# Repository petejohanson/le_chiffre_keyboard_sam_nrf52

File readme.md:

# DO NOT USE THIS YET

This is a fork of the awesome [Le Chiffre STM32 by Sporkus](https://github.com/sporkus/le_chiffre_keyboard_stm32/) refactored to
SAM L/D21 and a secondary nRF52805 BLE module that is COMPLETELY UNTESTED.

Don't print it, don't try it and ask why it doesn't work.

When it's ready and tested, this will be updated. Until then, just don't.

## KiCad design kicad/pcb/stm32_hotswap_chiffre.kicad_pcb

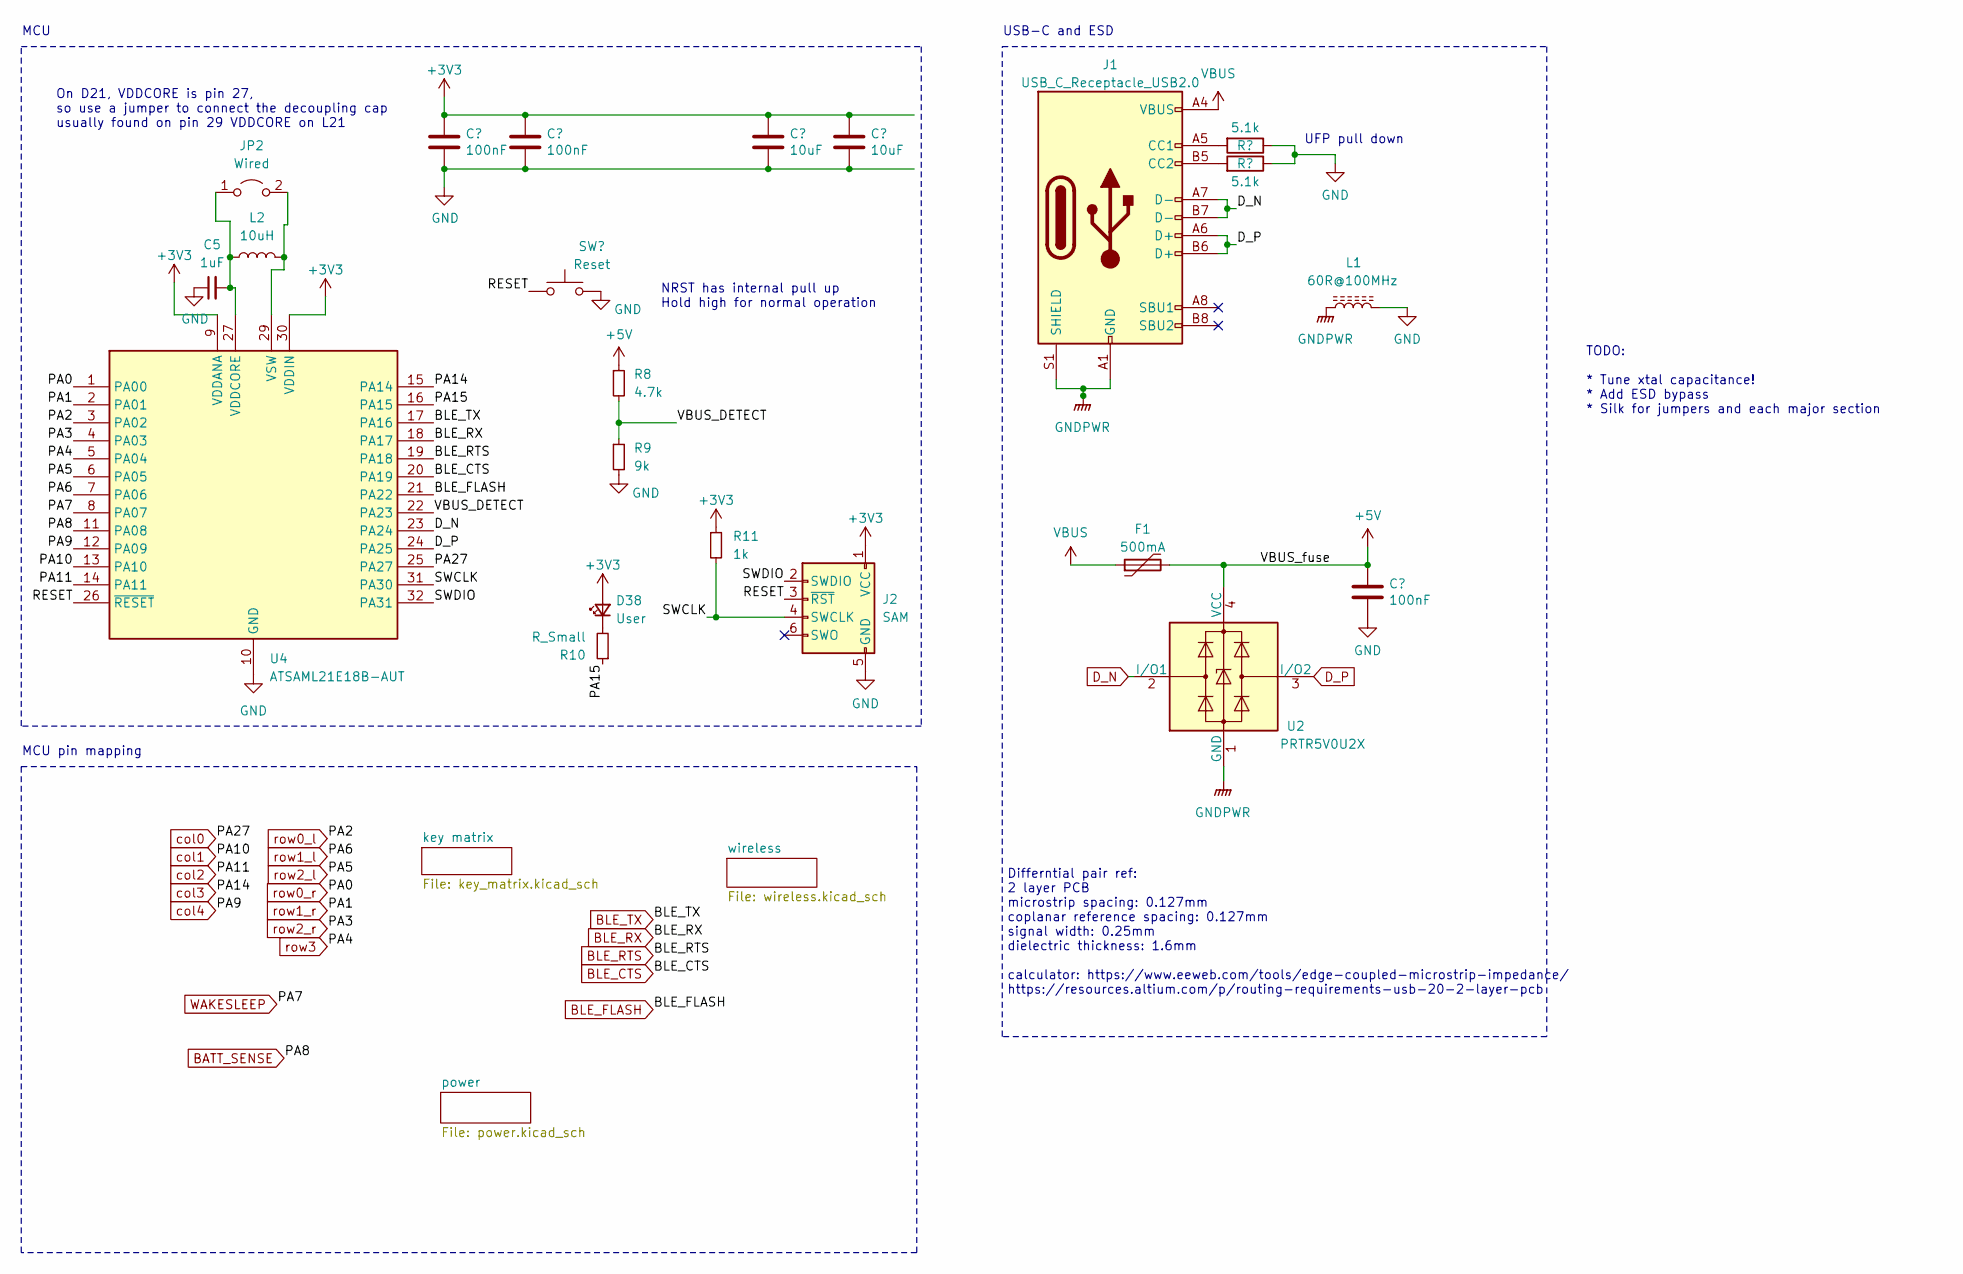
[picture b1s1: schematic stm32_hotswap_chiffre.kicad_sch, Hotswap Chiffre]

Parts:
C1, C2, C8: 100nF; C_0805_2012Metric; LCSC C38141
C3, C4: 10uF; C_0805_2012Metric; LCSC C17024
C5: 1uF; C_0805_2012Metric; LCSC C24123
D38: User; LED_0805_2012Metric; LCSC C84259
F1: 500mA; Fuse_1206_3216Metric; MPN BSMD1206-025-16V; LCSC C883119
J1: USB_C_Receptacle_USB2.0; USB_C_Receptacle_HRO_TYPE-C-31-M-12; MPN TYPE-C-31-M-12; JlcRotOffset 180
J2: SAM; CON_TC2030_outlined
JP2: Wired; SolderJumper-2_P1.3mm_Open_TrianglePad1.0x1.5mm
L1: 60R@100MHz; L_1206_3216Metric; MPN MLB3216-600P4A(f); LCSC C3033915
L2: 10uH; L_0805_2012Metric; LCSC C139245
R1, R2: 5.1k; R_0805_2012Metric; LCSC C118848
R8: 4.7k; R_0805_2012Metric; LCSC C228716
R9: 9k; R_0805_2012Metric; LCSC C2828721
R10: R_Small; R_0805_2012Metric; LCSC C2907256
R11: 1k; R_0805_2012Metric; LCSC C95781
SW37: Reset; SW_SPST_SKQG_WithoutStem; MPN SKQGABE010; LCSC C115351
U2: PRTR5V0U2X; SOT-143; MPN PRTR5V0U2X; LCSC C2827688
U4: ATSAML21E18B-AUT; TQFP-32_7x7mm_P0.8mm; MPN ATSAML21E18B-AUT; LCSC C2053723

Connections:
+5V: C8.1, F1.2, R8.1, U2.4 (VCC); also elsewhere on the board
/PA15: R10.1, U4.16 (PA15)
/RESET: J2.3 (~RST), SW37.1, U4.26 (~RESET)
/SWCLK: J2.4 (SWCLK), R11.2, U4.31 (PA30)
/SWDIO: J2.2 (SWDIO), U4.32 (PA31)
/VBUS_DETECT: R8.2, R9.1, U4.22 (PA23)
BATT_SENSE: U4.11 (PA08); also elsewhere on the board
BLE_CTS: U4.20 (PA19); also elsewhere on the board
BLE_FLASH: U4.21 (PA22); also elsewhere on the board
BLE_RTS: U4.19 (PA18); also elsewhere on the board
BLE_RX: U4.18 (PA17); also elsewhere on the board
BLE_TX: U4.17 (PA16); also elsewhere on the board
D_N: J1.A7 (D-), J1.B7 (D-), U2.2 (I/O1), U4.23 (PA24)
D_P: J1.A6 (D+), J1.B6 (D+), U2.3 (I/O2), U4.24 (PA25)
GNDPWR: J1.A1 (GND), J1.A12 (GND), J1.B1 (GND), J1.B12 (GND), J1.S1 (SHIELD), L1.1, U2.1 (GND)
unnamed: D38.1 (K), R10.2
unnamed: J1.A5 (CC1), R1.2
unnamed: J1.B5 (CC2), R2.2
unnamed: C5.2, JP2.1 (A), L2.1, U4.27 (VDDCORE)
unnamed: JP2.2 (B), L2.2, U4.29 (VSW)
VBUS: F1.1, J1.A4 (VBUS), J1.A9 (VBUS), J1.B4 (VBUS), J1.B9 (VBUS)
WAKESLEEP: U4.8 (PA07); also elsewhere on the board
col0: U4.25 (PA27); also elsewhere on the board
col1: U4.13 (PA10); also elsewhere on the board
col2: U4.14 (PA11); also elsewhere on the board
col3: U4.15 (PA14); also elsewhere on the board
col4: U4.12 (PA09); also elsewhere on the board
row0_l: U4.3 (PA02); also elsewhere on the board
row0_r: U4.1 (PA00); also elsewhere on the board
row1_l: U4.7 (PA06); also elsewhere on the board
row1_r: U4.2 (PA01); also elsewhere on the board
row2_l: U4.6 (PA05); also elsewhere on the board
row2_r: U4.4 (PA03); also elsewhere on the board
row3: U4.5 (PA04); also elsewhere on the board

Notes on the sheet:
On D21, VDDCORE is pin 27, so use a jumper to connect the decoupling cap usually found on pin 29 VDDCORE on L21
UFP pull down
MCU pin mapping
TODO: * Tune xtal capacitance! * Add ESD bypass * Silk for jumpers and each major section
MCU
USB-C and ESD
NRST has internal pull up Hold high for normal operation
Differntial pair ref: 2 layer PCB microstrip spacing: 0.127mm coplanar reference spacing: 0.127mm signal width: 0.25mm dielectric thickness: 1.6mm calculator: https://www.eeweb.com/tools/edge-coupled-microstrip-impedance/ https://resources.altium.com/p/routing-requirements-usb-20-2-layer-pcb

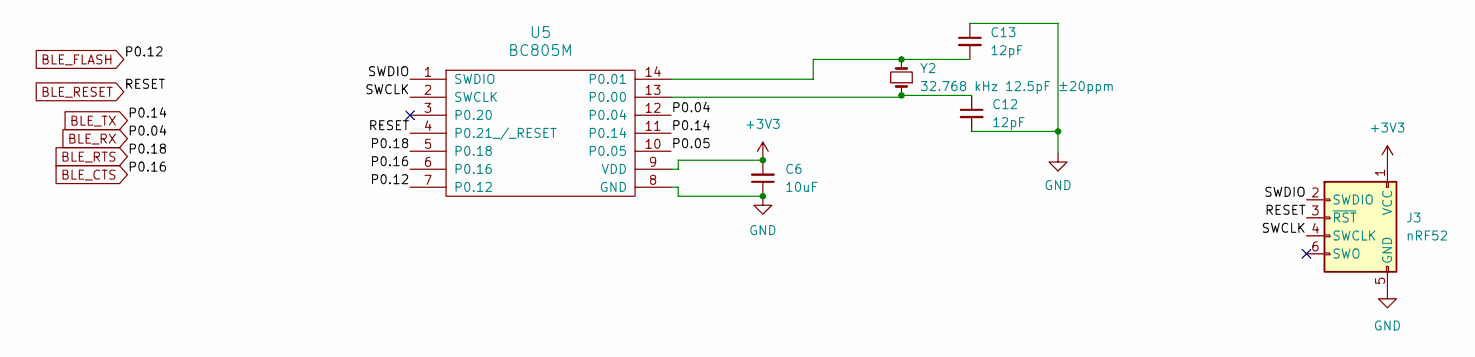
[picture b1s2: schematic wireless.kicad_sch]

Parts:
C6: 10uF; C_0805_2012Metric; LCSC C17024
C12, C13: 12pF; C_0805_2012Metric; LCSC C1792
J3: nRF52; CON_TC2030_outlined
U5: BC805M; MPN BC805M; LCSC C6751361
Y2: 32.768 kHz 12.5pF ±20ppm; Crystal_SMD_2012-2Pin_2.0x1.2mm_HandSoldering; LCSC C97603

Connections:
/wireless/P0.05: U5.10 (P0.05)
/wireless/SWCLK: J3.4 (SWCLK), U5.2 (SWCLK)
/wireless/SWDIO: J3.2 (SWDIO), U5.1 (SWDIO)
BLE_CTS: U5.6 (P0.16); also elsewhere on the board
BLE_FLASH: U5.7 (P0.12); also elsewhere on the board
BLE_RESET: J3.3 (~RST), U5.4 (P0.21_/_RESET)
BLE_RTS: U5.5 (P0.18); also elsewhere on the board
BLE_RX: U5.12 (P0.04); also elsewhere on the board
BLE_TX: U5.11 (P0.14); also elsewhere on the board
unnamed: C13.2, U5.14 (P0.01), Y2.2

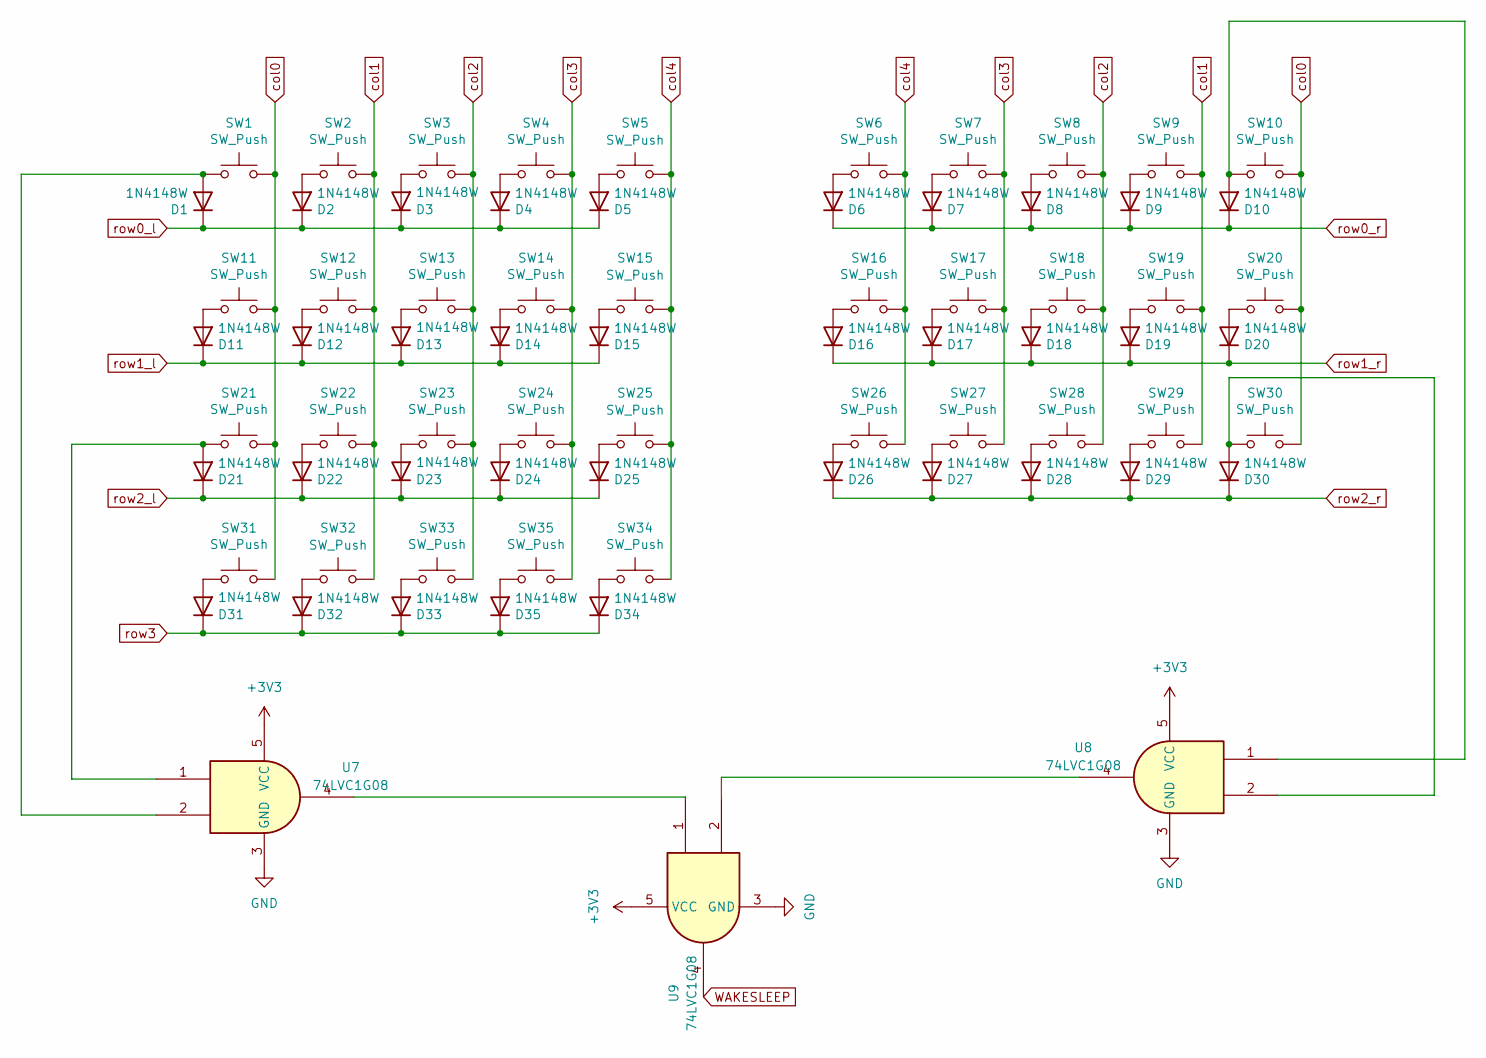
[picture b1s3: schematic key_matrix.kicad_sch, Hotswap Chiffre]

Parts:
D1, D2, D3, D4, D5, D11, D12, D13, D14, D15, D21, D22, D23, D24, D25, D31, D32: 1N4148W; D_SOD-123; MPN 1N4148W; JlcRotOffset 14
D6, D7, D8, D9, D10, D16, D17, D18, D19, D20, D26, D27, D28, D29, D30, D33, D34, D35: 1N4148W; D_SOD-123; MPN 1N4148W; JlcRotOffset -14
SW1, SW2, SW3, SW4, SW5, SW6, SW7, SW8, SW9, SW10, SW11, SW12, SW13, SW14, SW15, SW16, SW17, SW18, SW19, SW20, SW21, SW22, SW23, SW24, SW25, SW26, SW27, SW28, SW29, SW30, SW33: SW_Push; MX-Hotswap-Alps-1U
SW31, SW34: SW_Push; MX-Hotswap-Alps-1.25U
SW32, SW35: SW_Push; MX-Hotswap-Alps-2U
U7, U8, U9: 74LVC1G08; SOT-23-5_HandSoldering; MPN SN74LVC1G08DBVR; LCSC C7666

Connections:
unnamed: D1.2 (A), SW1.1, U7.2
unnamed: D2.2 (A), SW2.1
unnamed: D3.2 (A), SW3.1
unnamed: D4.2 (A), SW4.1
unnamed: D5.2 (A), SW5.1
unnamed: D6.2 (A), SW6.1
unnamed: D7.2 (A), SW7.1
unnamed: D8.2 (A), SW8.1
unnamed: D9.2 (A), SW9.1
unnamed: D10.2 (A), SW10.1, U8.1
unnamed: D11.2 (A), SW11.1
unnamed: D12.2 (A), SW12.1
unnamed: D13.2 (A), SW13.1
unnamed: D14.2 (A), SW14.1
unnamed: D15.2 (A), SW15.1
unnamed: D16.2 (A), SW16.1
unnamed: D17.2 (A), SW17.1
unnamed: D18.2 (A), SW18.1
unnamed: D19.2 (A), SW19.1
unnamed: D20.2 (A), SW20.1
unnamed: D21.2 (A), SW21.1, U7.1
unnamed: D22.2 (A), SW22.1
unnamed: D23.2 (A), SW23.1
unnamed: D24.2 (A), SW24.1
unnamed: D25.2 (A), SW25.1
unnamed: D26.2 (A), SW26.1
unnamed: D27.2 (A), SW27.1
unnamed: D28.2 (A), SW28.1
unnamed: D29.2 (A), SW29.1
unnamed: D30.2 (A), SW30.1, U8.2
unnamed: D31.2 (A), SW31.1
unnamed: D32.2 (A), SW32.1
unnamed: D33.2 (A), SW33.1
unnamed: D34.2 (A), SW34.1
unnamed: D35.2 (A), SW35.1
unnamed: U7.4, U9.1
unnamed: U8.4, U9.2
WAKESLEEP: U9.4; also elsewhere on the board
col0: SW1.2, SW10.2, SW11.2, SW20.2, SW21.2, SW30.2, SW31.2; also elsewhere on the board
col1: SW2.2, SW9.2, SW12.2, SW19.2, SW22.2, SW29.2, SW32.2; also elsewhere on the board
col2: SW3.2, SW8.2, SW13.2, SW18.2, SW23.2, SW28.2, SW33.2; also elsewhere on the board
col3: SW4.2, SW7.2, SW14.2, SW17.2, SW24.2, SW27.2, SW35.2; also elsewhere on the board
col4: SW5.2, SW6.2, SW15.2, SW16.2, SW25.2, SW26.2, SW34.2; also elsewhere on the board
row0_l: D1.1 (K), D2.1 (K), D3.1 (K), D4.1 (K), D5.1 (K); also elsewhere on the board
row0_r: D6.1 (K), D7.1 (K), D8.1 (K), D9.1 (K), D10.1 (K); also elsewhere on the board
row1_l: D11.1 (K), D12.1 (K), D13.1 (K), D14.1 (K), D15.1 (K); also elsewhere on the board
row1_r: D16.1 (K), D17.1 (K), D18.1 (K), D19.1 (K), D20.1 (K); also elsewhere on the board
row2_l: D21.1 (K), D22.1 (K), D23.1 (K), D24.1 (K), D25.1 (K); also elsewhere on the board
row2_r: D26.1 (K), D27.1 (K), D28.1 (K), D29.1 (K), D30.1 (K); also elsewhere on the board
row3: D31.1 (K), D32.1 (K), D33.1 (K), D34.1 (K), D35.1 (K); also elsewhere on the board

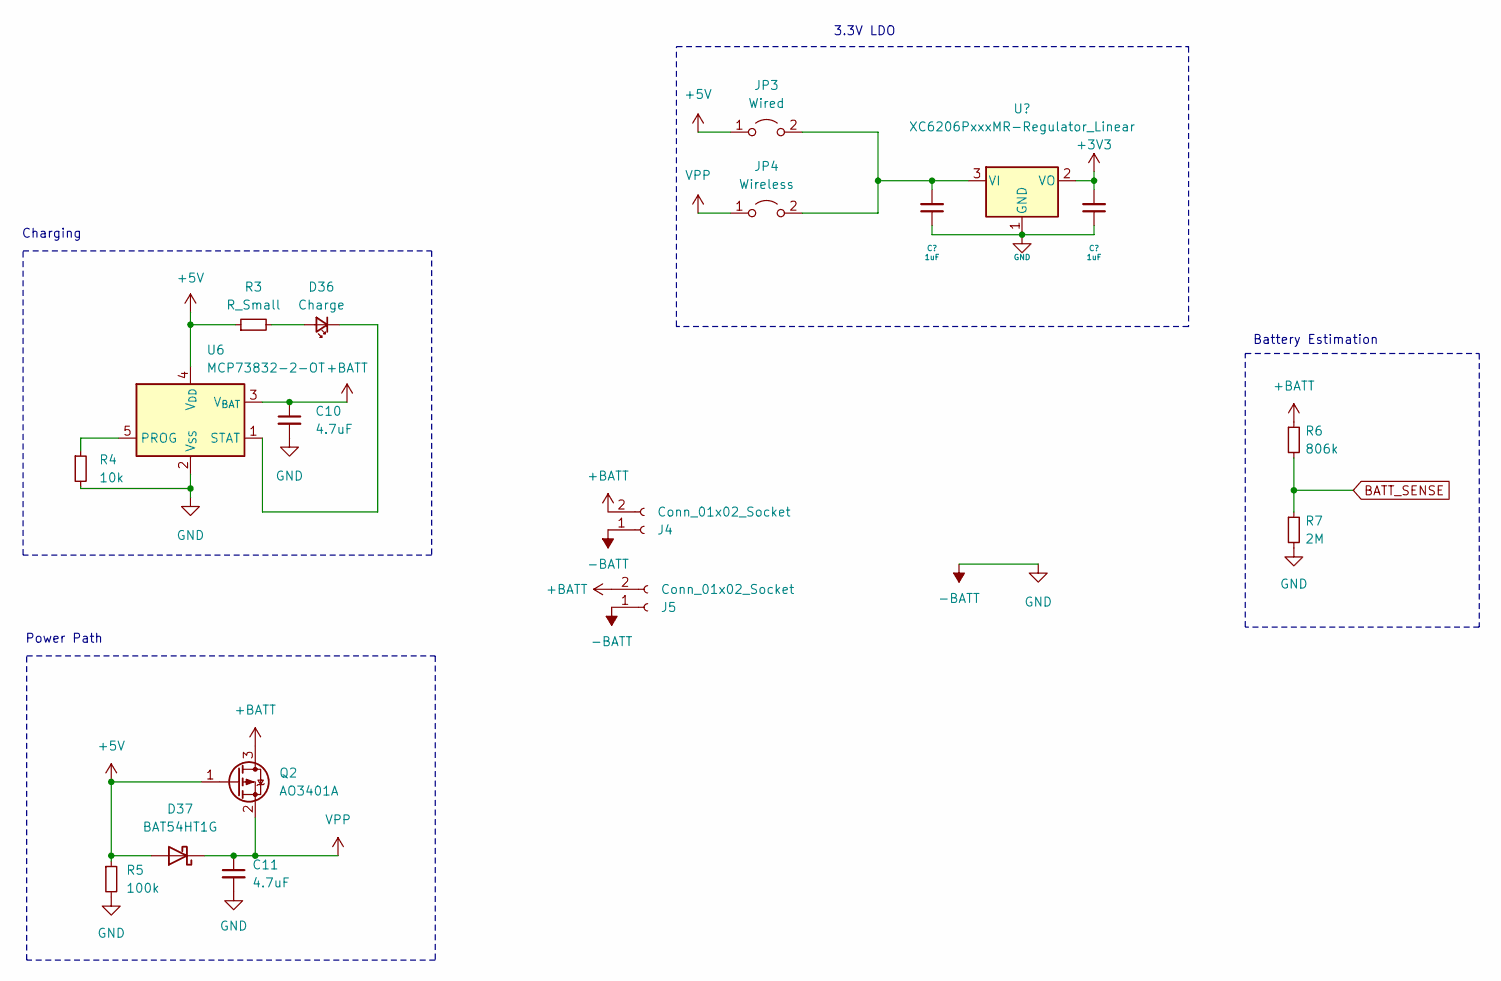
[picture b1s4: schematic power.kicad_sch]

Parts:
C10, C11: 4.7uF; C_0805_2012Metric; LCSC C1779
C12: 1uF; C_0805_2012Metric; LCSC C24123
D36: Charge; LED_0805_2012Metric; LCSC C2943978
D37: BAT54HT1G; D_SOD-323; MPN BAT54HT1G; LCSC C179609
J4: Conn_01x02_Socket; JST_SH_SM02B-SRSS-TB_1x02-1MP_P1.00mm_Horizontal; MPN SH-SM02B (SRSS)-TB
J5: Conn_01x02_Socket; PinHeader_1x02_P2.54mm_Vertical
JP3: Wired; SolderJumper-2_P1.3mm_Open_TrianglePad1.0x1.5mm
JP4: Wireless; SolderJumper-2_P1.3mm_Open_TrianglePad1.0x1.5mm
Q2: AO3401A; SOT-23; MPN AO3401A; LCSC C15127
R3: R_Small; R_0805_2012Metric; LCSC C2828866
R4: 10k; R_0805_2012Metric; LCSC C100047
R5: 100k; R_0805_2012Metric; LCSC C96346
R6: 806k; R_0805_2012Metric; LCSC C3016844
R7: 2M; R_0805_2012Metric; LCSC C228716
U3: XC6206PxxxMR-Regulator_Linear; SOT-23; MPN XC6206P332PR-G; LCSC C5446
U6: MCP73832-2-OT; SOT-23-5; MPN MCP73832-2-OT; LCSC C38066

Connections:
+5V: D37.2 (A), JP3.1 (A), Q2.1 (G), R3.1, R5.1, U6.4 (V_{DD}); also elsewhere on the board
+BATT: C10.1, J4.2, J5.2, Q2.3 (D), R6.1, U6.3 (V_{BAT})
BATT_SENSE: R6.2, R7.1; also elsewhere on the board
unnamed: D36.2 (A), R3.2
unnamed: D36.1 (K), U6.1 (STAT)
unnamed: R4.1, U6.5 (PROG)

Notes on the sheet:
Power Path
3.3V LDO
Battery Estimation
Charging

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
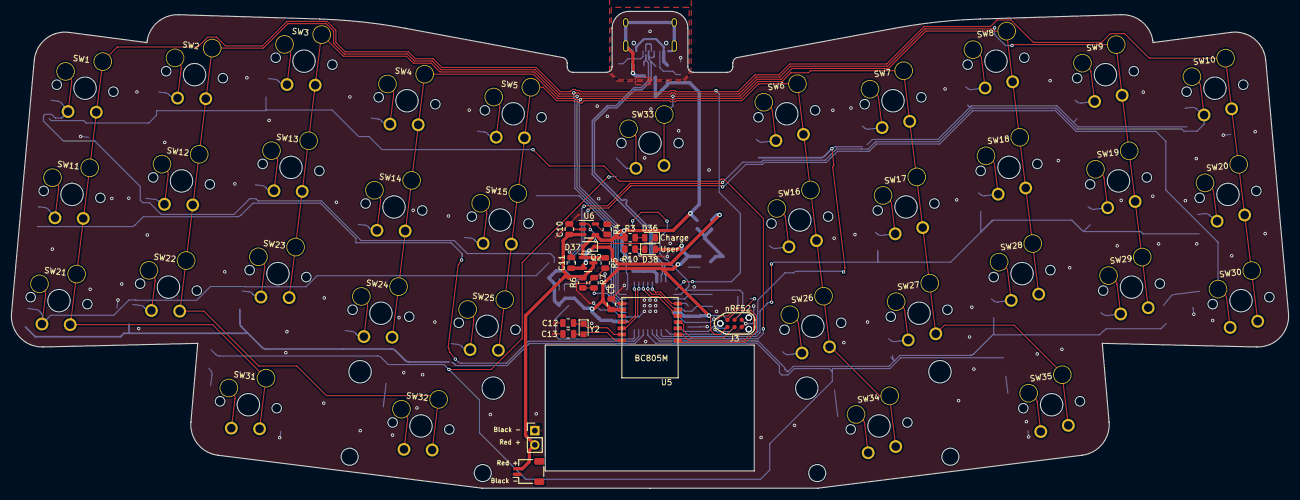
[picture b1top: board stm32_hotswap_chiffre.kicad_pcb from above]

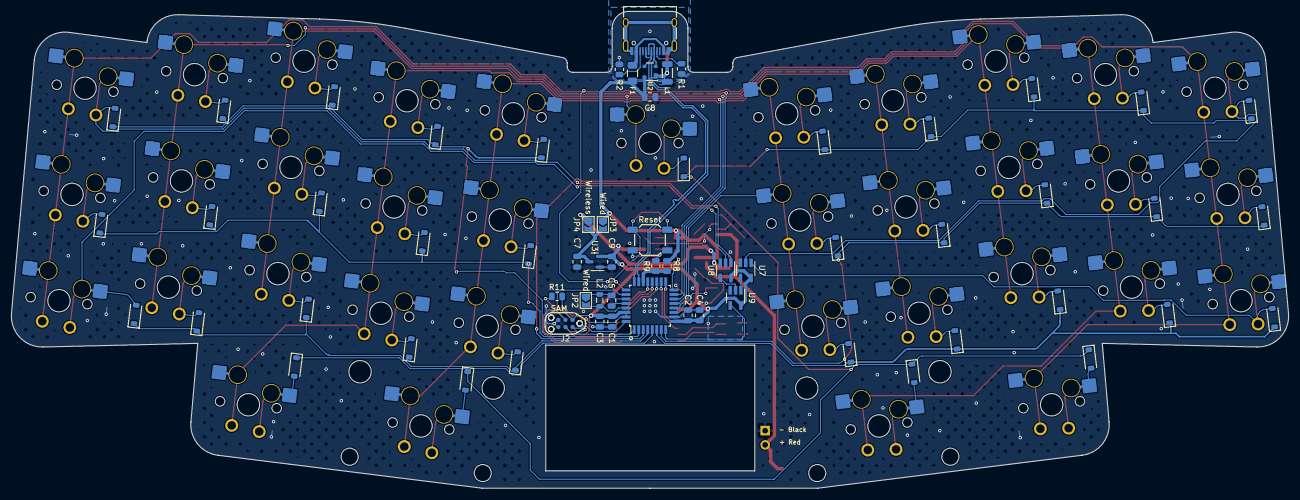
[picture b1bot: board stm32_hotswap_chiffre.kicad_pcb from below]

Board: 2 copper layers, 227.3 x 84.8 mm, 119 parts (63 on the bottom side), 84 nets.

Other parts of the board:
C7, C9: 1uF; C_0805_2012Metric

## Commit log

2023-12-11 Updated README.
2023-12-12 Edge cut fixes.
2023-12-19 Rework pins to use proper wake/interrupt pins for all matrix outputs, fix edge cuts.
2023-12-20 Minor cleanups of vias/traces and ERC happy.
2023-12-20 BOM tweaks, switch to horizontal JST SH.
2023-12-22 More BOM tweaks.
